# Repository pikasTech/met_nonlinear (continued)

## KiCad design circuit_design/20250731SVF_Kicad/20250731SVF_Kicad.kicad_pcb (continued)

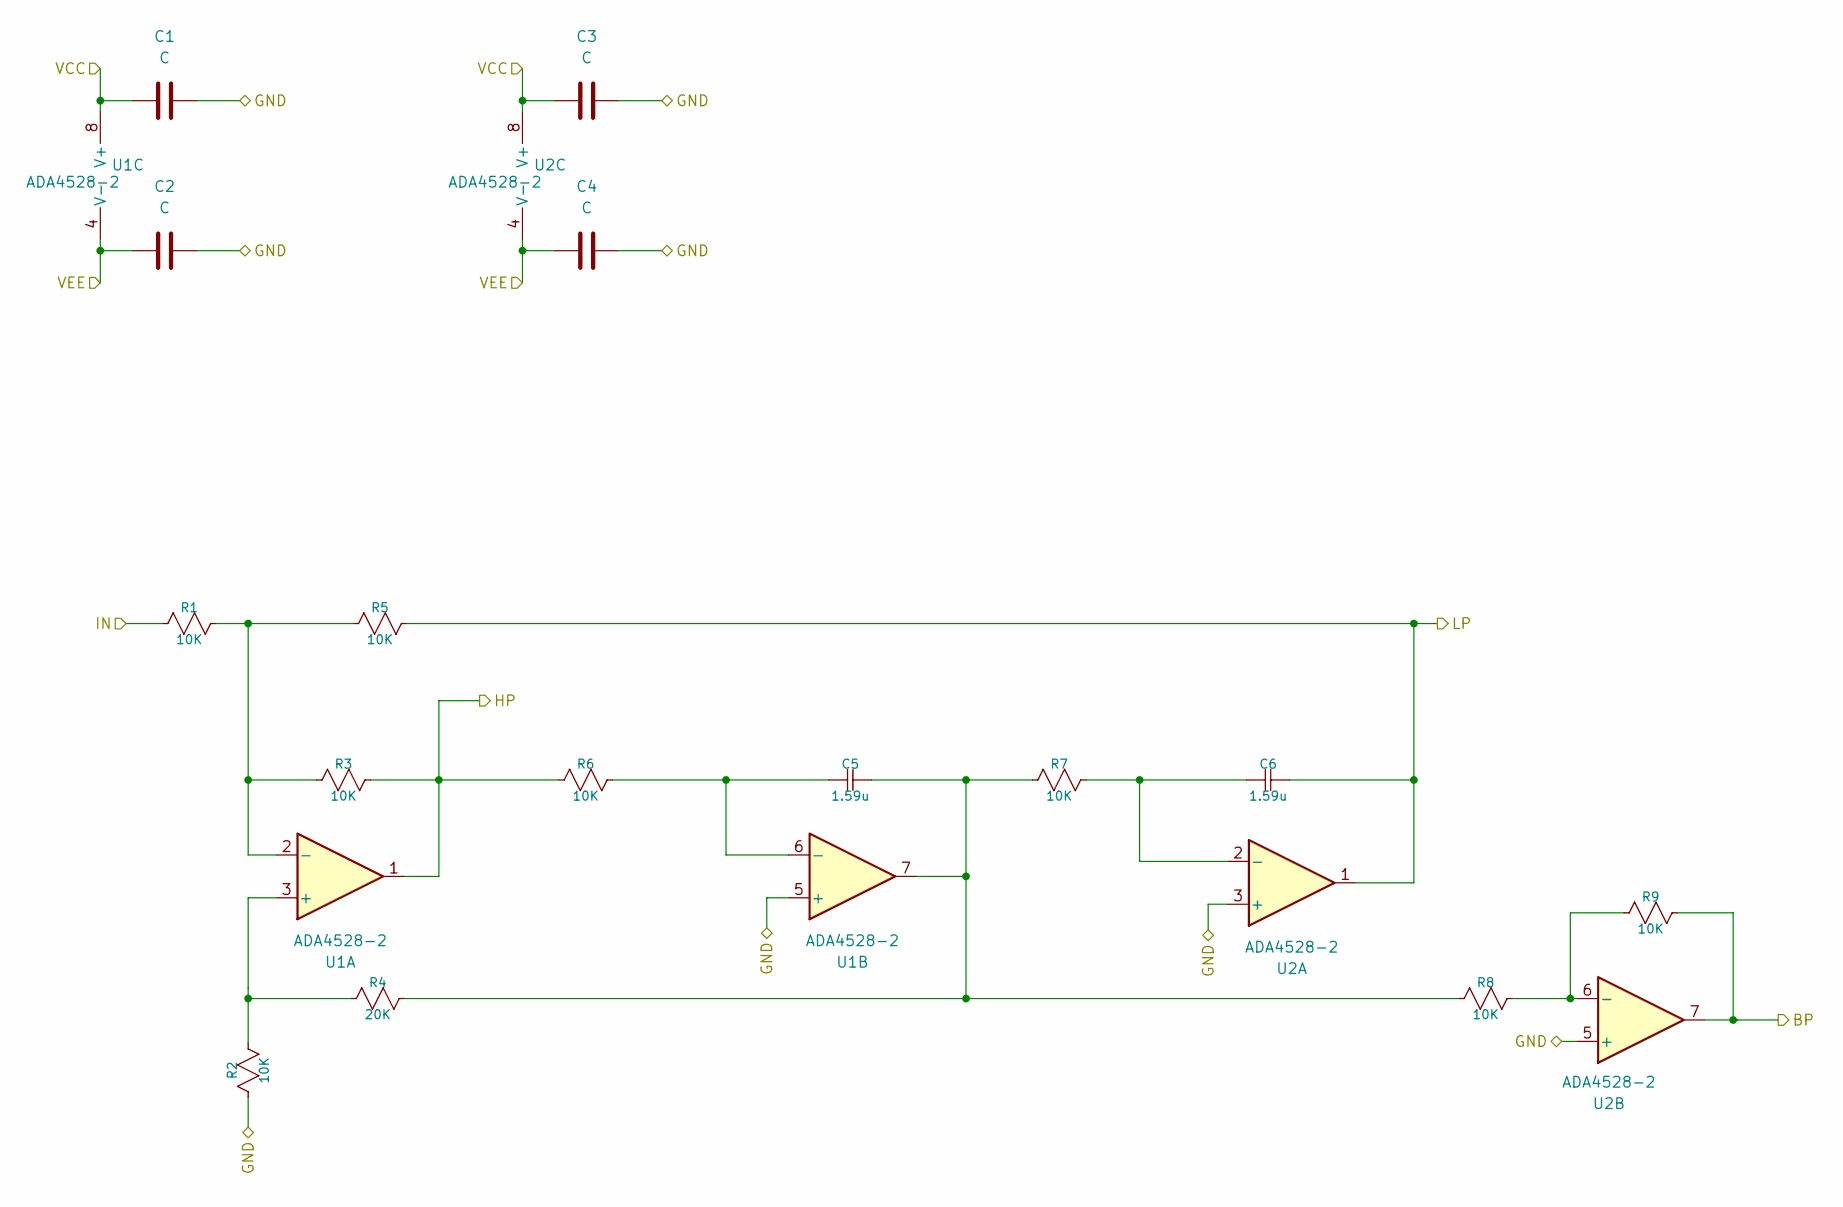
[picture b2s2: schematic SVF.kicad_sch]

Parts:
C1, C2, C3, C4: C; C_0805_2012Metric
C5, C6: 1.59u; C_0805_2012Metric
R1, R2, R3, R5, R6, R7, R8, R9: 10K; R_0805_2012Metric
R4: 20K; R_0805_2012Metric
U1, U2: ADA4528-2; MSOP-8_3x3mm_P0.65mm

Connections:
+V: C1.1, C3.1, U1.8 (V+), U2.8 (V+); also elsewhere on the board
-V: C2.1, C4.1, U1.4 (V-), U2.4 (V-); also elsewhere on the board
/SVF/IN: R1.2; also elsewhere on the board
GND: C1.2, C2.2, C3.2, C4.2, R2.2, U1.5 (+), U2.3 (+), U2.5 (+); also elsewhere on the board
unnamed: C5.1, R4.1, R7.2, R8.2, U1.7
unnamed: R2.1, R4.2, U1.3 (+)
unnamed: R1.1, R3.2, R5.2, U1.2 (-)
unnamed: C5.2, R6.1, U1.6 (-)
unnamed: C6.2, R7.1, U2.2 (-)
unnamed: R8.1, R9.2, U2.6 (-)
OUT1: R3.1, R6.2, U1.1; also elsewhere on the board
OUT2: R9.1, U2.7; also elsewhere on the board
OUT3: C6.1, R5.1, U2.1; also elsewhere on the board

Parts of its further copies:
C7, C8, C9, C10: C; C_0805_2012Metric
R10, R11, R12, R14, R15, R16, R17, R18: 10K; R_0805_2012Metric
R13: 20K; R_0805_2012Metric
U3, U4: ADA4528-2; MSOP-8_3x3mm_P0.65mm

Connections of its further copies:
+V: C7.1, C9.1, U3.8 (V+), U4.8 (V+); also elsewhere on the board
-V: C8.1, C10.1, U3.4 (V-), U4.4 (V-); also elsewhere on the board
/SVF/IN: R10.2; also elsewhere on the board
GND: C7.2, C8.2, C9.2, C10.2, R11.2, U3.5 (+), U4.3 (+), U4.5 (+); also elsewhere on the board
unnamed 5: R13.1, R16.2, R17.2, U3.7; also elsewhere on the board
unnamed: R11.1, R13.2, U3.3 (+)
unnamed: R10.1, R12.2, R14.2, U3.2 (-)
unnamed 13: R15.1, U3.6 (-); also elsewhere on the board
unnamed 14: R16.1, U4.2 (-); also elsewhere on the board
unnamed: R17.1, R18.2, U4.6 (-)
OUT4: R12.1, R15.2, U3.1; also elsewhere on the board
OUT5: R18.1, U4.7; also elsewhere on the board
OUT6: R14.1, U4.1; also elsewhere on the board

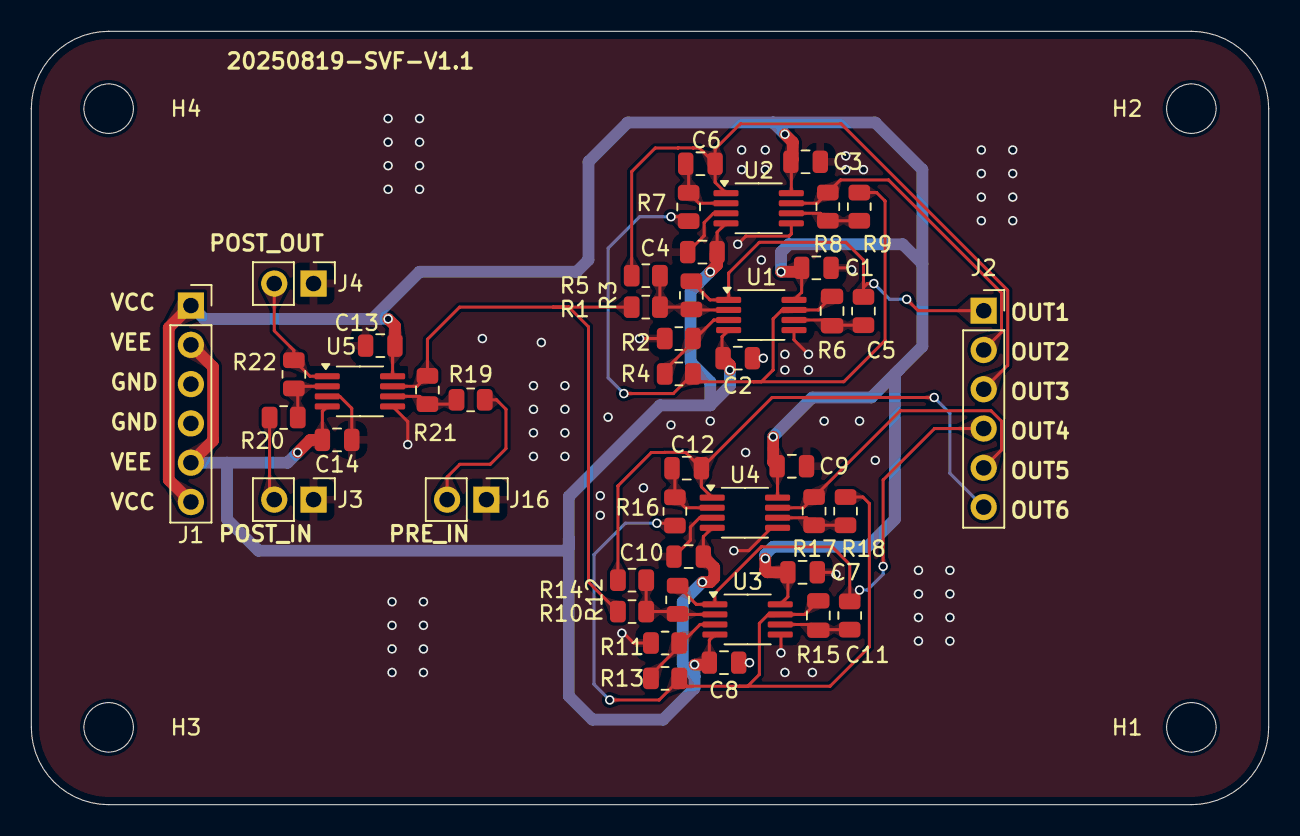
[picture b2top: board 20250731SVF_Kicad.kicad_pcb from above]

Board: 2 copper layers, 80.0 x 50.0 mm, 50 parts (0 on the bottom side), 27 nets.

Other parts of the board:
C11: C5; C_0805_2012Metric
C12: C6; C_0805_2012Metric

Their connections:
unnamed 5: C11.1; also elsewhere on the board
unnamed 13: C11.2; also elsewhere on the board
unnamed 14: C12.2; also elsewhere on the board
OUT6: C12.1; also elsewhere on the board

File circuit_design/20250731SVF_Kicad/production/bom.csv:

Designator,Footprint,Quantity,Value,LCSC Part #
"C1, C10, C13, C14, C2, C3, C4, C7, C8, C9",0805,10,C,
"C11, C5",0805,2,C5,
"C12, C6",0805,2,C6,
"J1, J2",PinSocket_1x06_P2.54mm_Vertical,2,Conn_01x06,
"J16, J3, J4",PinHeader_1x02_P2.54mm_Vertical,3,Conn_01x02,
"R1, R10, R11, R12, R14, R15, R16, R17, R18, R19, R2, R20, R21, R22, R3, R5, R6, R7, R8, R9",0805,20,10K,
"R13, R4",0805,2,20K,
"U1, U2, U3, U4, U5",MSOP-8_3x3mm_P0.65mm,5,ADA4528-2,

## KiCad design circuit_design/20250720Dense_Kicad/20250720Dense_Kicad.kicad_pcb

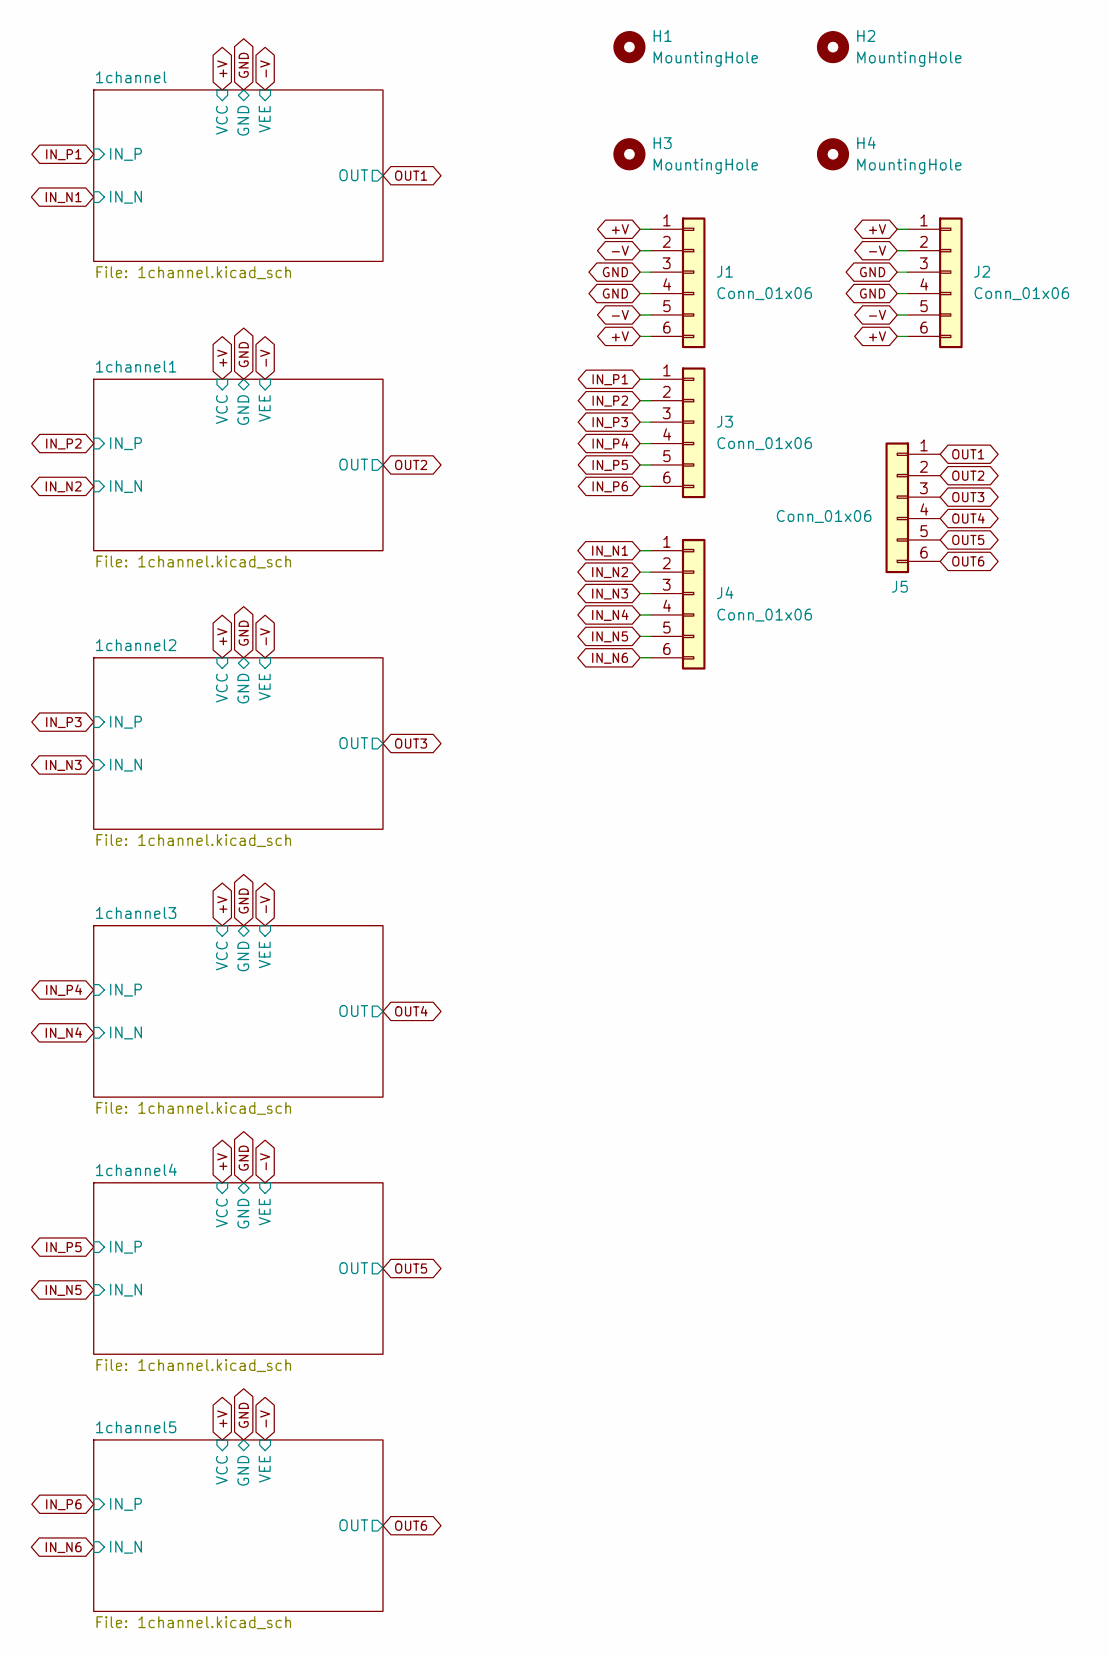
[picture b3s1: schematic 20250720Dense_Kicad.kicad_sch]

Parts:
H1, H2, H3, H4: MountingHole; MountingHole_3.2mm_M3
J1, J2, J3, J4, J5: Conn_01x06; PinSocket_1x06_P2.54mm_Vertical

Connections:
+V: J1.1, J1.6, J2.1, J2.6; also elsewhere on the board
-V: J1.2, J1.5, J2.2, J2.5; also elsewhere on the board
GND: J1.3, J1.4, J2.3, J2.4; also elsewhere on the board
IN_N1: J4.1; also elsewhere on the board
IN_N2: J4.2; also elsewhere on the board
IN_N3: J4.3; also elsewhere on the board
IN_N4: J4.4; also elsewhere on the board
IN_N5: J4.5; also elsewhere on the board
IN_N6: J4.6; also elsewhere on the board
IN_P1: J3.1; also elsewhere on the board
IN_P2: J3.2; also elsewhere on the board
IN_P3: J3.3; also elsewhere on the board
IN_P4: J3.4; also elsewhere on the board
IN_P5: J3.5; also elsewhere on the board
IN_P6: J3.6; also elsewhere on the board
OUT1: J5.1; also elsewhere on the board
OUT2: J5.2; also elsewhere on the board
OUT3: J5.3; also elsewhere on the board
OUT4: J5.4; also elsewhere on the board
OUT5: J5.5; also elsewhere on the board
OUT6: J5.6; also elsewhere on the board

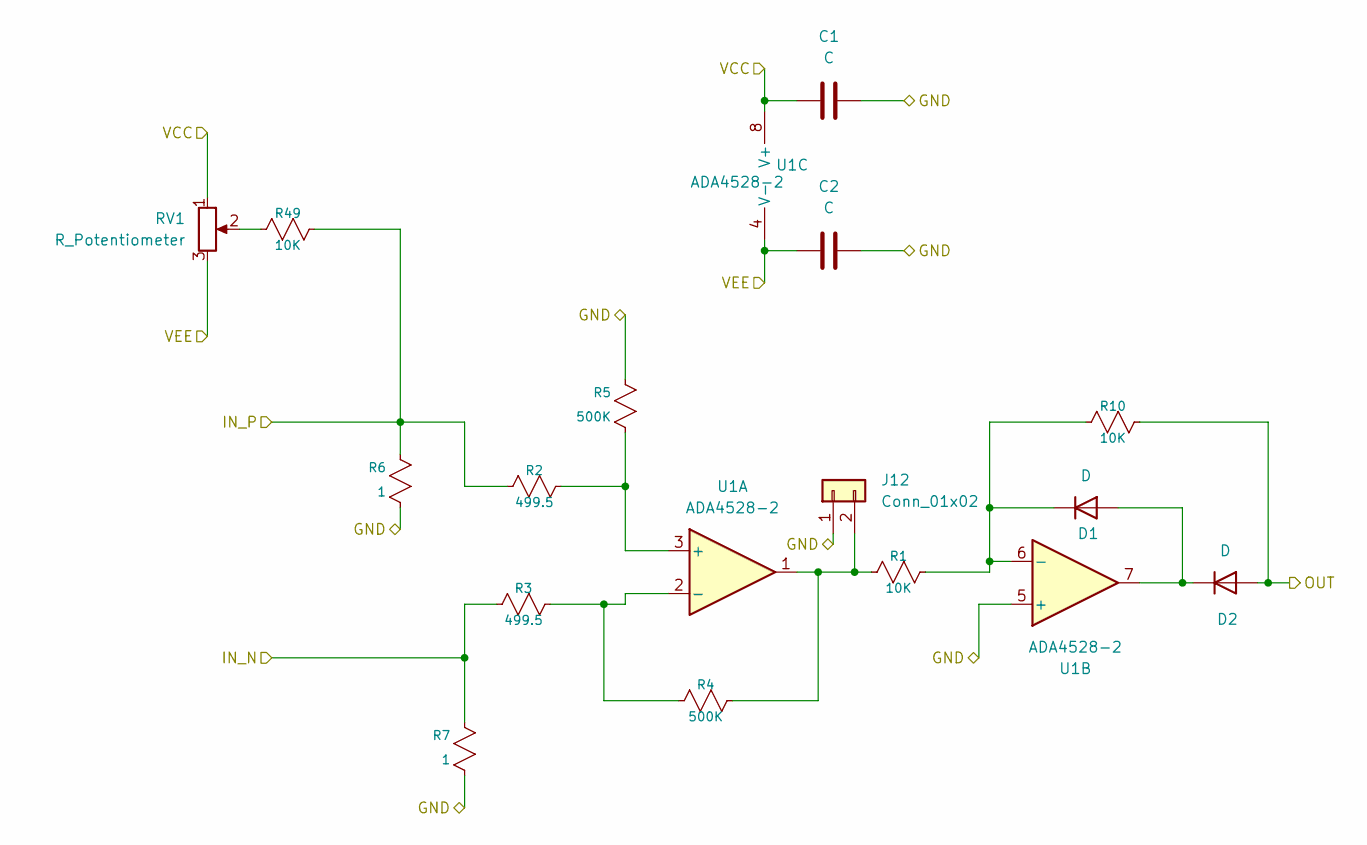
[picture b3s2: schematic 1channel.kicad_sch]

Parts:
C1, C2: C; C_0805_2012Metric
D1, D2: D; D_SOD-123F
J12: Conn_01x02; PinHeader_1x02_P2.54mm_Vertical
R1, R10, R49: 10K; R_0805_2012Metric
R2, R3: 499.5; R_0805_2012Metric
R4, R5: 500K; R_0805_2012Metric
R6, R7: 1; R_0805_2012Metric
RV1: R_Potentiometer; RES-ADJ-SMD_3224W
U1: ADA4528-2; MSOP-8_3x3mm_P0.65mm

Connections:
+V: C1.1, RV1.1, U1.8 (V+); also elsewhere on the board
-V: C2.1, RV1.3, U1.4 (V-); also elsewhere on the board
GND: C1.2, C2.2, J12.1, R5.2, R6.1, R7.1, U1.5 (+); also elsewhere on the board
IN_N1: R3.2, R7.2; also elsewhere on the board
IN_P1: R2.2, R6.2, R49.1; also elsewhere on the board
unnamed: D1.2 (A), D2.1 (K), U1.7
unnamed: D1.1 (K), R1.2, R10.1, U1.6 (-)
unnamed: J12.2, R1.1, R4.1, U1.1
unnamed: R49.2, RV1.2
unnamed: R2.1, R5.1, U1.3 (+)
unnamed: R3.1, R4.2, U1.2 (-)
OUT1: D2.2 (A), R10.2; also elsewhere on the board

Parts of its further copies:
C3, C4, C5, C6, C7, C8, C9, C10, C11, C12: C; C_0805_2012Metric
D3, D4, D5, D6, D7, D8, D9, D10, D11, D12: D; D_SOD-123F
J7, J14, J15, J16, J17: Conn_01x02; PinHeader_1x02_P2.54mm_Vertical
R8, R9, R17, R18, R25, R26, R33, R34, R41, R42: 1; R_0805_2012Metric
R11, R12, R19, R20, R27, R28, R35, R36, R43, R44: 499.5; R_0805_2012Metric
R13, R14, R21, R22, R29, R30, R37, R38, R45, R46: 500K; R_0805_2012Metric
R15, R16, R23, R24, R31, R32, R39, R40, R47, R48, R50, R51, R52, R53, R54: 10K; R_0805_2012Metric
RV2, RV3, RV4, RV5, RV6: R_Potentiometer; RES-ADJ-SMD_3224W
U2, U3, U4, U5, U6: ADA4528-2; MSOP-8_3x3mm_P0.65mm

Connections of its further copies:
+V: C3.1, C5.1, C7.1, C9.1, C11.1, RV2.1, RV3.1, RV4.1, RV5.1, RV6.1, U2.8 (V+), U3.8 (V+), U4.8 (V+), U5.8 (V+), U6.8 (V+); also elsewhere on the board
-V: C4.1, C6.1, C8.1, C10.1, C12.1, RV2.3, RV3.3, RV4.3, RV5.3, RV6.3, U2.4 (V-), U3.4 (V-), U4.4 (V-), U5.4 (V-), U6.4 (V-); also elsewhere on the board
GND: C3.2, C4.2, C5.2, C6.2, C7.2, C8.2, C9.2, C10.2, C11.2, C12.2, J7.1, J14.1, J15.1, J16.1, J17.1, R8.1, R9.1, R13.2, R17.1, R18.1, R21.2, R25.1, R26.1, R29.2, R33.1, R34.1, R37.2, R41.1, R42.1, R45.2, U2.5 (+), U3.5 (+), U4.5 (+), U5.5 (+), U6.5 (+); also elsewhere on the board
IN_N2: R9.2, R11.2; also elsewhere on the board
IN_N3: R18.2, R19.2; also elsewhere on the board
IN_N4: R26.2, R27.2; also elsewhere on the board
IN_N5: R34.2, R35.2; also elsewhere on the board
IN_N6: R42.2, R43.2; also elsewhere on the board
IN_P2: R8.2, R12.2, R50.1; also elsewhere on the board
IN_P3: R17.2, R20.2, R51.1; also elsewhere on the board
IN_P4: R25.2, R28.2, R52.1; also elsewhere on the board
IN_P5: R33.2, R36.2, R53.1; also elsewhere on the board
IN_P6: R41.2, R44.2, R54.1; also elsewhere on the board
unnamed: D3.2 (A), D4.1 (K), U2.7
unnamed: D3.1 (K), R15.2, R16.1, U2.6 (-)
unnamed: D5.2 (A), D6.1 (K), U3.7
unnamed: D5.1 (K), R23.2, R24.1, U3.6 (-)
unnamed: D7.2 (A), D8.1 (K), U4.7
unnamed: D7.1 (K), R31.2, R32.1, U4.6 (-)
unnamed: D9.1 (K), R39.2, R40.1, U5.6 (-)
unnamed: D9.2 (A), D10.1 (K), U5.7
unnamed: D11.2 (A), D12.1 (K), U6.7
unnamed: D11.1 (K), R47.2, R48.1, U6.6 (-)
unnamed: J7.2, R14.1, R15.1, U2.1
unnamed: J14.2, R22.1, R23.1, U3.1
unnamed: J15.2, R30.1, R31.1, U4.1
unnamed: J16.2, R38.1, R39.1, U5.1
unnamed: J17.2, R46.1, R47.1, U6.1
unnamed: R50.2, RV2.2
unnamed: R51.2, RV3.2
unnamed: R52.2, RV4.2
unnamed: R53.2, RV5.2
unnamed: R54.2, RV6.2
unnamed: R12.1, R13.1, U2.3 (+)
unnamed: R11.1, R14.2, U2.2 (-)
unnamed: R20.1, R21.1, U3.3 (+)
unnamed: R19.1, R22.2, U3.2 (-)
unnamed: R28.1, R29.1, U4.3 (+)
unnamed: R27.1, R30.2, U4.2 (-)
unnamed: R36.1, R37.1, U5.3 (+)
unnamed: R35.1, R38.2, U5.2 (-)
unnamed: R44.1, R45.1, U6.3 (+)
unnamed: R43.1, R46.2, U6.2 (-)
OUT2: D4.2 (A), R16.2; also elsewhere on the board
OUT3: D6.2 (A), R24.2; also elsewhere on the board
OUT4: D8.2 (A), R32.2; also elsewhere on the board
OUT5: D10.2 (A), R40.2; also elsewhere on the board
OUT6: D12.2 (A), R48.2; also elsewhere on the board

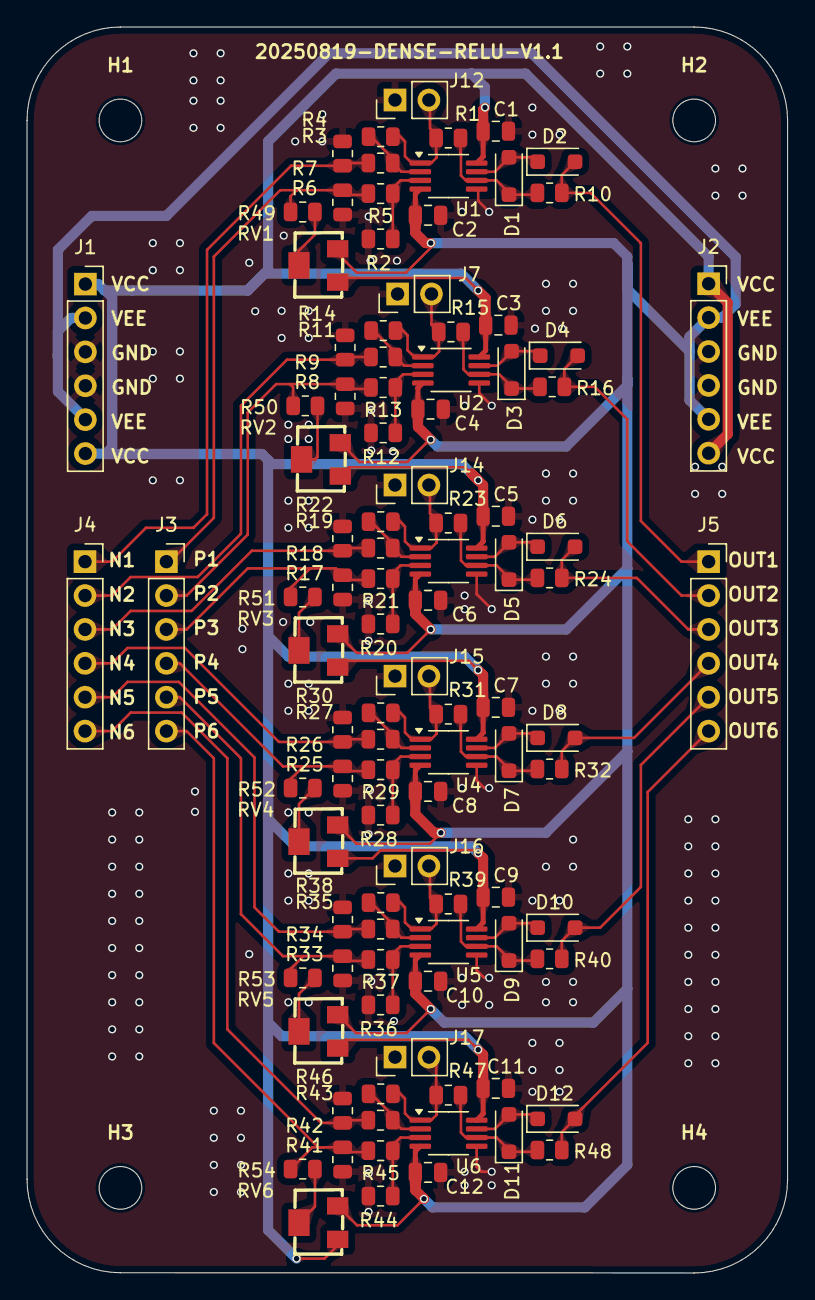
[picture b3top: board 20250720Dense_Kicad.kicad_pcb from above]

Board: 2 copper layers, 57.0 x 93.4 mm, 105 parts (0 on the bottom side), 57 nets.

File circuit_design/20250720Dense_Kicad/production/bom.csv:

Designator,Footprint,Quantity,Value,LCSC Part #
"C1, C10, C11, C12, C2, C3, C4, C5, C6, C7, C8, C9",0805,12,C,
"D1, D10, D11, D12, D2, D3, D4, D5, D6, D7, D8, D9",D_SOD-123F,12,D,
"J1, J2, J3, J4, J5",PinSocket_1x06_P2.54mm_Vertical,5,Conn_01x06,
"J12, J14, J15, J16, J17, J7",PinHeader_1x02_P2.54mm_Vertical,6,Conn_01x02,
"R1, R10, R15, R16, R23, R24, R31, R32, R39, R40, R47, R48, R49, R50, R51, R52, R53, R54",0805,18,10K,
"R11, R12, R19, R2, R20, R27, R28, R3, R35, R36, R43, R44",0805,12,499.5,
"R13, R14, R21, R22, R29, R30, R37, R38, R4, R45, R46, R5",0805,12,500K,
"R17, R18, R25, R26, R33, R34, R41, R42, R6, R7, R8, R9",0805,12,1,
"RV1, RV2, RV3, RV4, RV5, RV6",RES-ADJ-SMD_3224W,6,R_Potentiometer,
"U1, U2, U3, U4, U5, U6",MSOP-8_3x3mm_P0.65mm,6,ADA4528-2,

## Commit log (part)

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2025-10-11 MET Nonlinear - Clean repository without paper directory
2025-10-11 add project
2025-11-04 Add training information JSON file with detailed metrics
    - Included total epochs, minimum loss, and corresponding parameters.
    - Added minimum validation loss and power log loss metrics.
    - Documented learning rate statistics including max, min, and mean values.
2025-11-04 add new result
2025-11-04 准备绘制对比
2025-12-15 修改代码只允许ep绘图
2025-12-15 做了新的绘图
2025-12-23 增加svf-net-PS-5/360训练结果
2025-12-27 改目录结构
2025-12-27 正在引入E96量化引入的误差
2025-12-27 继续修复E96量化误差分析
2025-12-27 E96量化误差分析做了一部分
2025-12-28 E96模拟问题解决
2025-12-30 新增WNET5 Layers E96量化误差分析研究记录，包含研究概述、阶段调查、问题解决方案及最终成果总结
2025-12-30 beroefe merge
2025-12-30 before merge
2025-12-30 整理目录
2025-12-30 清理目录
2025-12-30 整理文档，编写 SVF 层误差分析的 principle
2025-12-30 SVF vs SVF OK
2025-12-30 处理SVF+DENSE结果不一致问题
2026-01-01 SVF_only 的误差分析基本 OK
2026-01-01 2,3,4层都完成了SVF_ONLY模式的误差的分析
2026-01-01 生成了报告
2026-01-02 更新conda 环境说明
2026-01-02 4个layers
2026-01-09 恢复了A1和B1
2026-01-09 Add configuration and update training states for WNET5 models
    - Created a new config.json file for WNET5_EFF2_B1 layer 2 with task information and frequency range.
    - Updated training_state.json for WNET5_EFF2_A1_PS-5_360 with a new timestamp.
    - Modified linear_response.json for WNET5_EFF2_B1 to reflect updated gains and fit parameters.
    - Updated training_state.json for WNET5_EFF2_B1 with a new timestamp.
2026-01-09 Add configuration files for WNET5 circuit validation layers
    - Created config.json files for layers 1 to 5 in the WNET5_EFF2_A1 project.
    - Each configuration includes task information, model project name, and frequency range.
    - Layer-specific descriptions added for clarity in the validation process.
2026-01-09 Refactor code structure for improved readability and maintainability
2026-01-09 修正报告中SVF电路元件参数表的格式
2026-01-14 更新.gitignore，删除无用的配置文件，修正训练状态时间戳
2026-01-14 Add training state JSON file for WaveNet5 model
    - Introduced a new JSON file to track the training state of the WaveNet5 model.
    - Includes details such as completed epochs, minimum loss values, current epoch, learning rate, and estimated training times.
    - This file will aid in monitoring and resuming training processes effectively.
2026-01-25 整理文档
2026-01-26 准备重构
2026-01-26 重构代码结构
2026-01-26 整理doc
2026-01-30 正在提高测试覆盖率
2026-02-03 Add unit tests for visualization modules and output log
    - Created a new test file for the image_data_process module with tests for calculate_drift and load_data functions.
    - Added tests for model_analysis, wnet5_circuit_validator, figure_paper, frequency_response_json_comparator, and data_viewer modules to ensure proper imports and function existence.
    - Generated a test output log capturing the results of the test session, including passed and failed tests.
2026-02-03 Refactor documentation paths for SVF layer error simulation reports
    - Updated report paths in various markdown files to reflect the new directory structure under `02_SVF层误差`.
    - Renamed and reorganized task reports to maintain consistency and clarity.
    - Ensured all references to previous report locations were corrected to the new format.
2026-02-04 回撤R1.15
2026-03-12 修复了 FRIKANh8u6l6无法启动的问题
2026-03-12 增加了 afmse 开始训练
2026-03-12 支持 afmse 和后训练
2026-03-12 修复modules
2026-03-27 准备转投MEASUREMENT
2026-03-27 增加了转投计划
2026-03-27 Remove test output file `test_output.txt` to clean up repository and reduce clutter.
2026-03-27 添加了调研任务
2026-03-28 Add raw literature, theory framework, and verified literature documents
    - Created `raw_literature.md` to compile recent research on KAN, Wiener models, frequency domain loss, drift compensation, architecture efficiency, and more.
    - Introduced `theory_framework.md` outlining the theoretical foundation for Wiener-KAN architecture claims, including empirical validations and efficiency arguments.
    - Established `verified_literature.md` to document core theories and applied technologies, highlighting key findings and contributions from various studies.
    - Added a test file `test.txt` for initial testing purposes.
2026-03-29 补充了很多文献调研
2026-03-29 准备执行CNNKAN
2026-03-29 增加了CNNKAN
2026-03-29 在尝试训练CNNKAN以及其文献调研
2026-03-29 开始做GAP支撑的文献整理
2026-03-30 补充了不少文献
2026-03-30 补全了GAP的文献
2026-03-31 补充了调研的文献
2026-03-31 正在准备进行分析
2026-03-31 规划者、执行者、审查者的架构正在运行
2026-03-31 提高并行度
2026-03-31 效果很好，审查出了很多虚假的支撑
2026-03-31 提出禁止跳过的要求
2026-03-31 提出修改意见
2026-03-31 现在要检验自我恢复的能力了
2026-03-31 检验审查能力
2026-03-31 复查了一夜
2026-04-01 准备做指标汇总
2026-04-01 增加了对正定和奇约束的配置控制
2026-04-02 增加了计算量估算
2026-04-02 更新AGENTS.md
2026-04-03 补充cimpl
2026-04-03 准备去601跑训练
2026-04-03 继续深挖了文献,测试了几个学习率
2026-04-03 fix conflect
2026-04-03 处理了3090掉卡的替补问题
2026-04-03 stm32 qemu work!
2026-04-03 stm32f405 + qemu OK
2026-04-03 支持lstm2qemu，还没有做MAE推理对齐
2026-04-03 支持导出波形
2026-04-04 lstm c_inference MAE OK
2026-04-04 c_inference ok
2026-04-04 QEMU中，FRIKAN+插值和FRIKAN无插值都比LSTMu16更优
2026-04-04 增加了GRN的c推理性能测试
2026-04-04 lstm-transformer 级别 OK
2026-04-04 add more 1k lr train
2026-04-04 更新了对比指标
2026-04-04 感觉现在反复调整越调越陷入泥潭，各种变量变得无限多
2026-04-05 add grnu16 e1k and lstm-transformer
2026-04-05 update e1k
2026-04-05 记录 CNNKAN 稳定训练与实验产物
2026-04-05 要改进CNNKAN
2026-04-07 CNNKAN 有进展
2026-04-09 在构建webui和指标分析infra
2026-04-09 解决了频域指标的一致性问题
2026-04-10 webui支持preset，改进了一些其他问题
2026-04-10 继续调优frikan_pure_afmae
2026-04-10 优化CLAUDE.md
2026-04-10 feat: add training log fetching and visualization
    - Introduced `fetchTrainingLog` API function to retrieve training logs for projects.
    - Added `LossCurvesView` component to visualize training and validation loss curves.
    - Updated `ComparisonView` to include loss curves as a selectable view mode.
    - Removed `ChartView` component as it is no longer used.
    - Enhanced `TableView` to display additional compute cost information, including warnings for unsupported layers.
    - Updated types to include `TrainingLogEntry` and `TrainingLogResponse` for better type safety.
2026-04-10 增加FRIMLP
2026-04-10 继续FRIMLP调参
2026-04-12 FRIMLP训练的差不多了
2026-04-12 feat: 增加训练后自动清理过期评估产物和刷新指标汇总功能
2026-04-12 Add comprehensive documentation for time series frequency analysis, validation boundaries, wave layered inference, and WNET5 circuit validation
    - Introduced `timeseries_frequency_analysis.md` detailing time domain data processing, frequency response reconstruction, and inference backend conventions.
    - Created `validation_boundaries.md` to outline experimental validation limits and extrapolation boundaries for project conclusions.
    - Added `wave_layered_inference.md` to define the role of `WaveData` in multi-backend inference and establish long-term agreements for layered model support.
    - Developed `wnet5_circuit_validation.md` to provide guidelines for WNET5 circuit validation, emphasizing th
2026-04-14 开始准备MN稿件
2026-04-15 还需要继续优化RNN
2026-04-19 Add ablation results and fix trainable IIR fast path
2026-04-20 整理了一些文档
2026-04-21 准备先重构qemu_keil
2026-04-21 彻底重构 board_inference 前
2026-04-21 重建后跑通了
2026-04-21 refactor: template board inference generators
    Move board inference C/H scaffolds into reusable templates, split sequence/frikan generator builders into smaller helpers, and keep the official qemu/keil benchmark outputs aligned with the R2.5 base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
2026-04-22 Add metrics and training info JSON files; implement tests for ablation study analysis
    - Created `metrics.json` and `training_info.json` files for the project `FRIKANh8u6l6_e1k_lr5e4_nopositive` containing detailed metrics and training information.
    - Added unit tests in `test_ablation_study.py` to verify the handling of missing metrics and null MAE values in the ablation study analysis.
    - Ensured that missing metrics are reported as errors in the generated markdown report.
2026-04-22 Add comprehensive documentation for paper methods and evaluation processes
    - Introduced "paper_edge_inference_evaluation_method.md" detailing the evaluation methods for edge device inference, including experimental objectives, design principles, and necessary formulas.
    - Added "paper_horizontal_comparison_method.md" to outline the methodology for horizontal comparison experiments, emphasizing experimental design, shared control variables, and formal grouping.
    - Created "paper_method_draft_writing.md" to establish writing norms for drafting paper methods, focusing on structure, content requirements, and project-specific constraints.
    - Developed "paper_metric_calculation_method.md" to standard
2026-04-22 创建了中间稿和draft
2026-04-23 准备做超参数敏感性分析
2026-04-24 正在做正文的修改计划，另外超参数灵敏度还没有跑完，有的还有 OOM
2026-04-24 docs: add hyperparameter sensitivity analysis
2026-04-24 准备merge参数灵敏度分析
2026-04-24 正文review过了，大问题修了，还有其他问题
2026-04-25 docs: update paper figures and traceability workflow
2026-04-25 消融实验的组织、公式严谨性等还要再改
2026-04-27 正在突出On-Board Real-Time
2026-04-28 清理 08_IIR_AB
2026-04-30 手改了摘要部分
2026-05-05 feat: add UniDesk MET training microservice
2026-05-06 feat: add unidesk met queue workflow
2026-05-06 feat: expose met project details for unidesk
2026-05-06 docs: refine MET dataset and experimental setup description in paper
    This commit reorganizes the experimental design section to follow a Problem -> Solution structure and accurately reflects the software generation of the ideal reference sequence from measured inputs,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
2026-05-13 支持ps-5/190和ps-5/360的假频全频带绘图
2026-05-14 add file
2026-05-22 准备启动小论文的翻译
2026-05-31 准备做字数压缩和最后的投稿准备
2026-06-08 docs: update MN manuscript submission draft
2026-06-08 chore: update paper review workflow
2026-06-15 准备提交
